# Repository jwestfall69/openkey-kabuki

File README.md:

# openkey-kabuki
* [Overview](#overview)
* [Project Status](#project-status)
* [Supported Games](#supported-games)
  * [Mitchell](#mitchell)
  * [CPS 1.5 (QSound CPU)](#cps-15-qsound-cpu)
* [Hardware](#hardware)
  * [PCB Manufacturing](#pcb-manufacturing)
  * [BOM](#bom)
  * [Assembly](#assembly)
* [Programming](#programming)
  * [Hardware](#hardware-1)
  * [Software](#software)
* [Installation](#installation)
  * [Mitchell DBS Identify/Removal](#mitchell-dbs-identifyremoval)
  * [CPS 1.5 (QSound CPU) DBS Identify/Removal](#cps-15-qsound-cpu-dbs-identifyremoval)

## Overview
This is an opensource/hardware implementation of an on the fly kabuki CPU key programmer that consists of a PCB that sits between the CPU socket and the kabuki CPU.  The kabuki CPU is found in Mitchell and CPS 1.5 arcade boards and contains keys for decrypting/decoding the program roms.

Installed:<br>

This project is providing the same functionality as [Undamned's InfiniKey-Kabuki](https://www.arcade-projects.com/threads/infinikey-kabuki.8338/).  The lack of supply is what prompted me to make openkey-kabuki.  If they ever end up coming back in stock please consider purchasing those to support [Undamned](https://www.arcade-projects.com/forums/temple-of-the-undamned.77/)'s work.

Details on *how* to program a kabuki CPU's key data can be found in [Eduardo Cruz](http://arcadehacker.blogspot.com/)'s [write up](http://arcadehacker.blogspot.com/2014/11/capcom-kabuki-cpu-intro.html) and [youtube video](https://www.youtube.com/watch?v=9t-9hQEOjLI).

Details on *what* to program can be found in MAME's decryption code for the [kabuki CPU](https://github.com/mamedev/mame/blob/master/src/mame/capcom/kabuki.cpp#L73).

## Project Status
**PCB:** I would consider the design PCB done at this point.  I'm open to any input on changes/improvements as this is my first PCB design.

**Firmware:** Need to get untested games tested

**Documentation:** Done

## Supported Games
openkey-kabuki supports either having a 5 position switch or using solder jumpers for picking which game key to use.  For the switch, ensure the switches are fully set.  You should hear a click sound as you change the position.

Below is a list of supported games and what switches/jumpers must be used for each.

#### Mitchell
| Switch<br>12345 | Program ROM Labels | MAME Sets | Game Names | Tested / Working |
|-----------------|:------------------:|-----------|--------------|:-----------------:|
| 00000 | BLE<br>BLJ | block<br>blockj | Block Block | YES (conversion)|
| 00001 | CBJ | cbasebal | Capcom Baseball | |
| 00010 | CW | cworld | Capcom World | YES (conversion) |
| 00011 | D2 | dokaben2 | Dokaben 2 | YES (conversion) |
| 00100 | DB | dokaben | Dokaben | YES (conversion) |
| 00101 | MG2 | mgakuen2 | Mahjong Gakuen 2 Gakuen-chou no Fukushuu | YES |
| 00110 | MG3 | marukin | Super Marukin-Ban | YES (conversion) |
| 00111 | PK<br>PKO | pkladiesl<br>pkladies | Poker Ladies | YES (conversion) |
| 01000 | PWE<br>PWJ<br>PWU | pang<br>pompingw<br>bbros | Pang<br>Pomping World<br>Buster Bros | YES |
| 01001 | Q2 | hatena | Adventure Quiz 2 - Hatena? no Daibouken | YES (conversion) |
| 01010 | Q3 | qtono1 | Quiz Tonosama no Yabou | YES |
| 01011 | Q4 | qsangoku | Quiz Sangokushi | YES |
| 01100 | SPE | spang | Super Pang (World) | YES |
| 01101 | SPJ | spangj | Super Pang (Japan) | YES |
| 01110 | SPU | sbbros | Super Buster Bros | YES |
| 01111 | ??? | ??? | Ashita Tenki ni Naare  (place holder) | |

#### CPS 1.5 (QSound CPU)
| Switch<br>12345 | Program ROM Labels | MAME Sets | Game Names | Tested / Working |
|-----------------|:------------------:|-----------|--------------|:-----------------:|
| 10000 | CDE<br>CDJ<br>CDT<br>CDU | dino<br>dinoj<br>dinoa<br>dinou | Cadillacs and Dinosaurs | |
| 10001 | MBE<br>MBJ<br>MBU<br>MBDE<br>MBDJ | slammast<br>mbomberj<br>slammastu<br>mbombrd<br>mbombrdj | Saturday Night Slam Masters<br>Muscle Bomber<br>Muscle Bomber Duo | YES |
| 10010 | PSE<br>PSH<br>PSJ<br>PSE | punisher<br>punisherh<br>punisherj<br>punisheru | Punisher | YES |
| 10011 | TK2A<br>TK2E<br>TK2J<br>TK2U | wofa<br>wof<br>wofj<br>wofu | Warriors of Fate | YES |

**IMPORTANT**: There is a compatibility issue with the older 92636D-3 revision of the D board.  Specifics on this issue can be found [here](https://www.arcade-projects.com/threads/openkey-kabuki-project.23571/post-370690)

When openkey-kabuki is used on a 92636D-3 board revision you will get:

  * "RAM ERROR" screen on Warriors of Fate
  * "1111 EXCEPTION" screen on Slam Masters
  * "NG" screen on Muscle Bomber Duo
  * A black screen on Punisher and C&D

Thus far I've only seen WOF using this older version of the D board.

The compatibility issue was tracked down to a bug in the D9K1 PAL thats on 92636D-3.  The fix is to upgrade that PAL to D9K2, which is found on the newer revision of the D board (92636D-5).

## Hardware
---
#### PCB Manufacturing
You will want to pick **0.8mm PCB thickness** instead of the default of 1.6mm.  A 1.6mm thick PCB will make the legs on openkey-kabuki to be a little to short and cause it to not be fully secure in the CPU socket.

I've been using [jlcpcb](https://jlcpcb.com/) for PCB manufacturing.  The only real downside I've seen with them is they charge a fee (~$17) if you pick a color other then green or black with 0.8mm PCB thickness.  Also watch out, by default they will add an order number to the silk screen unless you tell them not to.

#### BOM
| Description | Part Number | DigiKey | Mouser | Notes |
|-------------|-------------|---------|--------|-------|
| 40 Pin Dip Machine Socket | Adam Tech ICM-640-1-GT-HT | [2057-ICM-640-1-GT-HT-ND](https://www.digikey.com/en/products/detail/adam-tech/ICM-640-1-GT-HT/9832971) | | The specific part number isn't required, but it must be a machined 40 pin dip socket with the cross members in the same locations as seen in the picture at the top of this page. This [part](https://www.aliexpress.us/item/2251832711755702.html) from Aliexpress worked for me as well. |
| ATtiny404 20Mhz | ATTINY404-SSN | [ATTINY404-SSN-ND](https://www.digikey.com/en/products/detail/microchip-technology/ATTINY404-SSN/9947546) | [556-ATTINY404-SSNR](https://www.mouser.com/ProductDetail/Microchip-Technology-Atmel/ATTINY404-SSNR?qs=F5EMLAvA7IAEqD7Aw0z%252B9Q%3D%3D) | Other ATtiny tinyAVR 0/1/2-series models should be viable as well.  The code compiles to just over 1K in size, so any that have 2k or more of flash should work.  Just note I have only tested with 404s |
| 100nf / 0.1uf SMD Ceramic Capacitor 0805 Size | | | | |
| 5 Position Slide Switch | Würth Elektronik 416131160805 | [732-3855-2-ND](https://www.digikey.com/en/products/detail/w%C3%BCrth-elektronik/416131160805/3174531) | [710-416131160805](https://www.mouser.com/ProductDetail/Wurth-Elektronik/416131160805?qs=2kOmHSv6VfT1rqUsojuQog%3D%3D) | **Optional** not needed if using the solder jumpers to pick the game.  This part more then doubles the BOM cost. |

**NOTE**: Additional components maybe needed if you need to revert any previously made desuicide modifications to the arcade PCB.  Check the Installation section at the bottom for details.

#### Assembly
The first thing you should do is a test fit of the socket into the openkey-kabuki PCB.  I came across a couple PCBs in a batch that didn't fit and wasn't until after I had soldered the SMD components that I found this out.

As you can see in the first socket in the picture below the pins start out wide then go skinny.  Normally the wide part is used to keep the socket up off a board, however the openkey-kabuki PCB has extra wide through holes to allow it to sit flush with the plastic part of the socket.  Doing this allows the pins from the socket to be long enough to fit properly into the CPU socket of the arcade board.

You should solder the SMD components first.  Take special care to void getting any solder into any of the socket through holes.

  * If you install the dip switch block I would advise testing it
  * If you are using the solder jumpers instead, these can be done now or after everything is fully assembled.

When soldering the socket its best to not use a ton of solder.  The below picture is a board where the socket hasn't been soldered in yet.

Note the small gap between the through holes and socket pins.  Solder will naturally want to wick up into that gap.  I generally just use enough solder so that the gap around the socket pin becomes filled.

Once you have completed soldering the socket you should check the skinny part of the pins to verify there aren't any solder blobs on them.  These could cause damage to the CPU socket.

## Programming
#### Hardware
Programming is done with a UPDI programmer.  I've been using this one:

[Serial UPDI Programmer for ATmega 0-Series, or ATtiny 0-Series or 1-Series, or AVR DA or AVR DB](https://www.amazon.com/dp/B09X64YRLD?psc=1&ref=ppx_yo2ov_dt_b_product_details)

Note: This programmer (and likely others) has a switch for 3.3V and 5V.  Set it to 5V.

The openkey-kabuki programming port is setup so you can wedge the pins from the above programmer directly into them to programming.

Of course be sure you properly orient the board so the labeled pin/holes match up.  vcc to vcc, gnd to gnd, and updi to updi.

#### Software
For software I've been using the [Arduino IDE](https://www.arduino.cc/en/software/OldSoftwareReleases) with [megaTinyCore](https://github.com/SpenceKonde/megaTinyCore), which adds support for tinyAVR 0/1/2-Series MCUs.

**NOTE**: The makers of megaTinyCore currently recommend using Arduino IDE version 1.8.13 for best compatibility.  2.0 definitely does not work!

To install the megaTinyCore you, should just need to add http://drazzy.com/package_drazzy.com_index.json to "Additional Boards Manager URLs" in the settings for the Arduino IDE.

From there you need to configure the board/programming settings.  I've been using these:

## Installation
Prior to installing openkey-kabuki you should verify you don't have the [The Dead Battery Society](http://www.arcadecollecting.com/dead/) mod installed on your mitchell or cps 1.5 D board.  Part of the DBS mod is to tie pin 28 of the kabuki CPU to GND.  This pin is normally fed voltage from the battery/vcc to supply the CPU with power for its internal ram holding the key data.  openkey-kabuki will not function unless this is reverted.

Below is how you can identify if the DBS mod is been installed and how to remove it.

#### Mitchell DBS Identify/Removal
This is what a dead battery society mod will look like

 * R33 (1k ohm resistor) is missing
 * Right through hole of R33 is bridged to the lower right
 * Those pins on the program roms are soldered together and have a wire from them to a pin on the cpu
 * Modified program roms

 All of these things will need to be reverted in order to use openkey-kabuki.  This is what an unmodified board should look like.

#### CPS 1.5 (QSound CPU) DBS Identify/Removal

This is what the dead battery society mod will look like on the QSound board of a cps 1.5 game.

Top Side:<br>

* R33 (1 ohm resistor 0805 size) is missing
* C12 (100nf capacitor 0805 size) is replaced with a jumper
* Modified QSound program rom

Bottom Side:<br>

* Wire running from QSound program rom pin 30 to Kabuki CPU pin 27
* Cut trace between QSound program rom pins 30 and 31

There will be additional changes specific to slam masters / muscle bomber which are not covered above.

Once reverted it should look like this

Top Side:<br>

Bottom Side:<br>

Its hard to tell from the picture, but pins 30 and 31 on the QSound program rom are jumper'd together.

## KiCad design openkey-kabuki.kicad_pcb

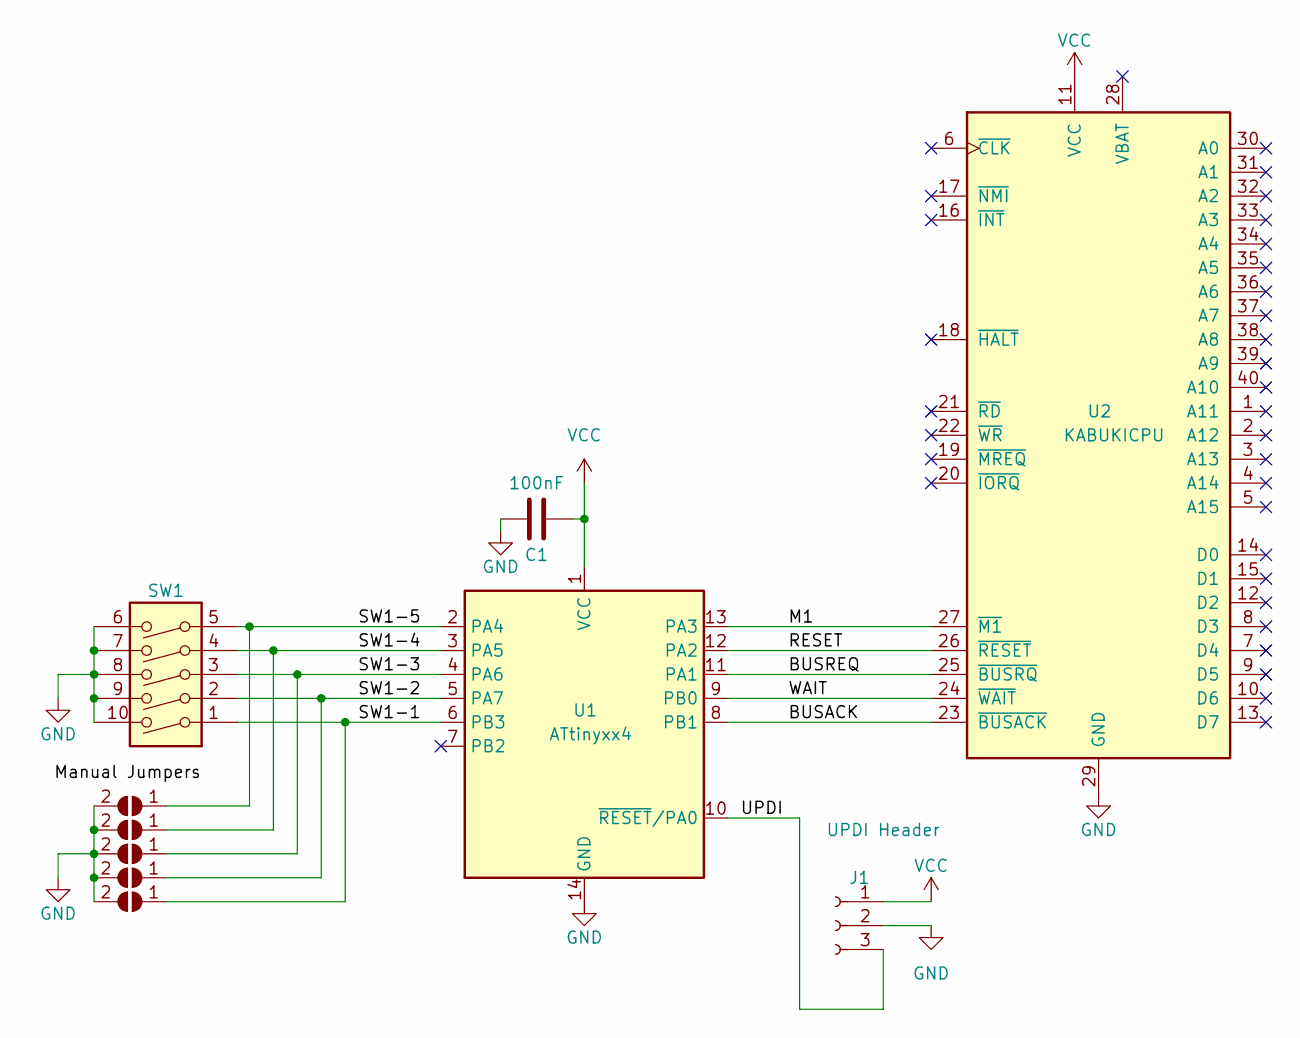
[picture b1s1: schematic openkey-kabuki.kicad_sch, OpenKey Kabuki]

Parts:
C1: 100nF; C_0805_2012Metric_Pad1.18x1.45mm_HandSolder
J1: UPDI Header; PinHeader_1x03_P2.54mm_Vertical
JP1, JP2, JP3, JP4, JP5: SolderJumper_2_Open; SolderJumper-2_P1.3mm_Open_Pad1.0x0.6mm
SW1: Wurth Elektronik 416131160805; SW_DIP_SPSTx05_Slide_Wurth_416131160805_W7.62mm_P1.27mm
U1: ATtinyxx4; SOIC-14_3.9x8.7mm_P1.27mm
U2: KABUKICPU; DIP-40_W15.24mm_Socket_Wide_Holes

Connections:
/BUSACK: U1.8 (PB1), U2.23 (~BUSACK)
/BUSREQ: U1.11 (PA1), U2.25 (~BUSRQ)
/M1: U1.13 (PA3), U2.27 (~M1)
/RESET: U1.12 (PA2), U2.26 (~RESET)
/SW1-1: JP1.1 (A), SW1.1, U1.6 (PB3)
/SW1-2: JP2.1 (A), SW1.2, U1.5 (PA7)
/SW1-3: JP3.1 (A), SW1.3, U1.4 (PA6)
/SW1-4: JP4.1 (A), SW1.4, U1.3 (PA5)
/SW1-5: JP5.1 (A), SW1.5, U1.2 (PA4)
/UPDI: J1.3, U1.10 (~RESET/PA0)
/WAIT: U1.9 (PB0), U2.24 (~WAIT)
GND: C1.2, J1.2, JP1.2 (B), JP2.2 (B), JP3.2 (B), JP4.2 (B), JP5.2 (B), SW1.6, SW1.7, SW1.8, SW1.9, SW1.10, U1.14 (GND), U2.29 (GND)
VCC: C1.1, J1.1, U1.1 (VCC), U2.11 (VCC)

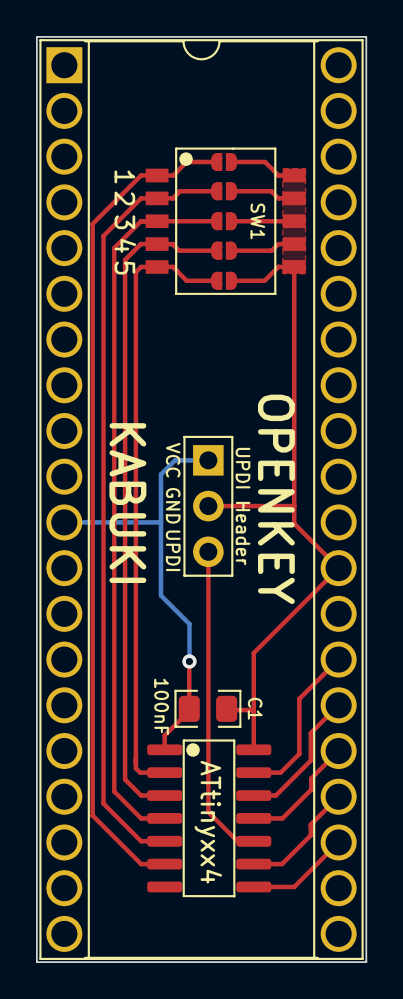
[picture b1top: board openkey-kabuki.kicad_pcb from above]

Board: 2 copper layers, 18.3 x 51.4 mm, 10 parts (0 on the bottom side), 13 nets.

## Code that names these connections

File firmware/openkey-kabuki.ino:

#include <avr/sleep.h>

// PIN 8 (PIN_B1) <=> Kabuki PIN 23 (BUSACK)
#define SET_BUSACK    PORTB.OUTSET = PIN1_bm
#define CLR_BUSACK    PORTB.OUTCLR = PIN1_bm

// PIN 9 (PIN_B0) <=> Kabuki PIN 24 (WAIT)
#define SET_WAIT      PORTB.OUTSET = PIN0_bm
#define CLR_WAIT      PORTB.OUTCLR = PIN0_bm

// PIN 10 (PIN_A0) used for UPDI (ATtiny programming)

// PIN 11 (PIN_A1) <=> Kabuki PIN 25 (BUSREQ)
#define SET_BUSREQ    PORTA.OUTSET = PIN1_bm
#define CLR_BUSREQ    PORTA.OUTCLR = PIN1_bm

// PIN 12 (PIN_A2) <=> Kabuki PIN 26 (RESET)
#define SET_RESET     PORTA.OUTSET = PIN2_bm
#define CLR_RESET     PORTA.OUTCLR = PIN2_bm

// PIN 13 (PIN_A3) <=> Kabuki PIN 27 (M1)
#define SET_M1        PORTA.OUTSET = PIN3_bm
#define CLR_M1        PORTA.OUTCLR = PIN3_bm

// First 4 fields come from mame @
// https://github.com/mamedev/mame/blob/master/src/mame/capcom/kabuki.cpp#L73
// mem_mask field comes from Eduardo Cruz (ArcadeHacker). 
// https://github.com/ArcadeHacker/ArcadeHacker_Kabuki/blob/master/ArcadeHacker_Kabuki.ino#L33
typedef struct game_key_t {
  uint32_t swap_key1;
  uint32_t swap_key2;
  uint16_t address_key;
   uint8_t xor_key;
  uint16_t mem_mask;
} game_key;

#define MAX_GAME_NUM   20
game_key game_keys[MAX_GAME_NUM + 1] = {
  // mitchell games                                      dsw
  //   skey1       skey2     addr    xor   mask         12345
  { 0x02461357, 0x64207531, 0x0002, 0x01, 0x7000 },  // 00000 [BLx] Block Block (BLE, BLJ)
  { 0x01234567, 0x76543210, 0x6548, 0x24, 0x7000 },  // 00001 [CBJ] Capcom Baseball
  { 0x04152637, 0x40516273, 0x5751, 0x43, 0x7000 },  // 00010 [CW]  Capcom World
  { 0x76543210, 0x01234567, 0xaa55, 0xa5, 0x7000 },  // 00011 [D2]  Dokaben 2
  { 0x76543210, 0x01234567, 0xaa55, 0xa5, 0x7000 },  // 00100 [DB]  Dokaben
  { 0x76543210, 0x01234567, 0xaa55, 0xa5, 0x7000 },  // 00101 [MG2] Mahjong Gakuen 2 Gakuen-chou no Fukushuu
  { 0x54321076, 0x54321076, 0x4854, 0x4f, 0x7000 },  // 00110 [MG3] Super Marukin-Ban
  { 0x76543210, 0x01234567, 0xaa55, 0xa5, 0x7000 },  // 00111 [PKx] Poker Ladies (PK, PKO)
  { 0x01234567, 0x76543210, 0x6548, 0x24, 0xf000 },  // 01000 [PWx] Pang / Buster Bros / Pomping World (PWE, PWJ, PWU)
  { 0x45670123, 0x45670123, 0x5751, 0x43, 0x7000 },  // 01001 [Q2]  Adventure Quiz 2 Hatena ? no Dai-Bouken
  { 0x12345670, 0x12345670, 0x1111, 0x11, 0x7000 },  // 01010 [Q3]  Quiz Tonosama no Yabou
  { 0x23456701, 0x23456701, 0x1828, 0x18, 0x7000 },  // 01011 [Q4]  Quiz Sangokushi
  { 0x45670123, 0x45670123, 0x5852, 0x43, 0x7000 },  // 01100 [SPE] Super Pang World
  { 0x45123670, 0x67012345, 0x55aa, 0x5a, 0x7000 },  // 01101 [SPJ] Super Pang Japan
  { 0x45670123, 0x45670123, 0x2130, 0x12, 0x7000 },  // 01110 [SPU] Super Buster Bros
  { 0x00000000, 0x00000000, 0x0000, 0x00, 0x0000 },  // 01111 [???] Ashita Tenki ni Naare (unknown)

  // cps1.5 games                                        dsw
  //   skey1       skey2     addr    xor   mask         12345
  { 0x76543210, 0x24601357, 0x4343, 0x43, 0xff00 },  // 10000 [CDx] Cadillacs and Dinosaurs (CDE, CDJ, CDT, CDU)
  { 0x54321076, 0x65432107, 0x3131, 0x19, 0xff00 },  // 10001 [MBx] Slam Masters (MBDE, MBDJ, MBE, MBJ, MBU)
  { 0x67452103, 0x75316024, 0x2222, 0x22, 0xff00 },  // 10010 [PSx] Punisher (PS, PSE, PSH, PSU)
  { 0x01234567, 0x54163072, 0x5151, 0x51, 0xff00 },  // 10011 [TKx] Warrior of Fate (TK2A, TK2E, TK2J, TK2U)

  // bad dsw value / zero key
  { 0x00000000, 0x00000000, 0x0000, 0x00, 0x0000 }
};

// doing bit shifting takes a variable amount
// of time depending on the how far the shift
// is.  Using the below lookup table to keep
// a consistent clock period when masking a
// bit to send. 
uint32_t masks[32] = {
  0x00000001, 0x00000002, 0x00000004, 0x00000008,
  0x00000010, 0x00000020, 0x00000040, 0x00000080,
  0x00000100, 0x00000200, 0x00000400, 0x00000800,
  0x00001000, 0x00002000, 0x00004000, 0x00008000,
  0x00010000, 0x00020000, 0x00040000, 0x00080000,
  0x00100000, 0x00200000, 0x00400000, 0x00800000,
  0x01000000, 0x02000000, 0x04000000, 0x08000000,
  0x10000000, 0x20000000, 0x40000000, 0x80000000,
};

void setup() {
  
  // wait a bit for other IC's on the board to get
  // in their inital states
  delay(100);

  // wait for the WAIT pin on the kabuki to go high
  // before we do anything
  while(!PORTB.IN & PIN0_bm) { }
  
  // set the pins to kabuki as outputs
  PORTA.DIR = PIN1_bm | PIN2_bm | PIN3_bm;
  PORTB.DIR = PIN0_bm | PIN1_bm;

  // stage #1: set initial output states
  // https://www.youtube.com/watch?v=9t-9hQEOjLI&t=754s
  CLR_RESET;
  CLR_WAIT;
  CLR_BUSREQ;
  SET_M1;
  SET_BUSACK;

  // enable pull-ups on dsw pins
  PORTA.PIN4CTRL |= PORT_PULLUPEN_bm;  // PIN 2 (PIN_PA4) <=> DSW5
  PORTA.PIN5CTRL |= PORT_PULLUPEN_bm;  // PIN 3 (PIN_PA5) <=> DSW4
  PORTA.PIN6CTRL |= PORT_PULLUPEN_bm;  // PIN 4 (PIN_PA6) <=> DSW3
  PORTA.PIN7CTRL |= PORT_PULLUPEN_bm;  // PIN 5 (PIN_PA7) <=> DSW2
  PORTB.PIN3CTRL |= PORT_PULLUPEN_bm;  // PIN 6 (PIN_PB3) <=> DSW1

  // stage #2: door knock #1
  // https://www.youtube.com/watch?v=9t-9hQEOjLI&t=871s
  for(int i = 0;i < 3;i++) {
    SET_BUSREQ;
    CLR_BUSREQ;
  }

  // stage #3: unlock key
  // https://www.youtube.com/watch?v=9t-9hQEOjLI&t=1274s
  send_data(0xb7a45, 20, -1);

  // stage #4: door knock #2
  // https://www.youtube.com/watch?v=9t-9hQEOjLI&t=1433s
  for(int i = 0;i < 10;i++) {
    CLR_M1;
    SET_M1;
  }

  uint8_t game_num = read_dsw();
  if(game_num > MAX_GAME_NUM) {
    game_num = MAX_GAME_NUM;
  }

  // stage #5: 108-bit programming
  // https://www.youtube.com/watch?v=9t-9hQEOjLI&t=1518s
  send_data(0x0, 20, -1);
  send_data(game_keys[game_num].address_key, 16, -1);

  // mame swap keys are 32bit, but the actual swap key is 24bit.
  // the conversion process is to drop the top bit from each nibble.
  // below we are looping over each nibble and only sending the
  // lower 3 bits.
  for(int start_bit = 30; start_bit > 0; start_bit -= 4) {
    send_data(game_keys[game_num].swap_key2, 3, start_bit);
  }

  for(int start_bit = 30; start_bit > 0; start_bit -= 4) {
    send_data(game_keys[game_num].swap_key1, 3, start_bit);
  }

  send_data(game_keys[game_num].xor_key, 8, -1);
  send_data(game_keys[game_num].mem_mask, 16, -1);

  // set all pins to be inputs
  PORTA.DIR = 0;
  PORTB.DIR = 0;

  // power down
  set_sleep_mode(SLEEP_MODE_PWR_DOWN);
  sleep_enable();
  sleep_cpu();
}

void loop() {
  while(1) {}
}

// send bits of data starting at start_bit and going MSB to LSB.
// if start_bit is -1, send the last LSB num_bits bits of the data
void send_data(uint32_t data, int8_t num_bits, int8_t start_bit) {
  num_bits--;

  if(start_bit == -1) {
    start_bit = num_bits;
  }

  while(num_bits >= 0) {
    uint32_t bit = data & masks[start_bit];
    if(bit) {
      SET_M1;
    } else {
      CLR_M1;
    }
    CLR_BUSACK;
    SET_BUSACK;
    num_bits--;
    start_bit--;
  }
}

// DSW1 = PB3 = bit4
// DSW2 = PA7 = bit3
// DSW3 = PA6 = bit2
// DSW4 = PA5 = bit1
// DSW5 = PA4 = bit0
uint8_t read_dsw() {
  uint8_t dsw = 0;

  // negate the bits since we are using
  // pull-ups, "on"s will be low
  uint8_t porta = PORTA.IN ^ 0xff;
  uint8_t portb = PORTB.IN ^ 0xff;

  dsw = porta >> 4;
  dsw = dsw | ((portb & 0b0001000) << 1);
  return dsw;
}

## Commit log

2022-10-11 initial checkin
2022-10-11 Add openkey-kicad-library as submodule
2022-10-11 board checkin
2022-10-11 Move hardware bits under hardware dir
2022-10-11 Checkin firmware
2022-10-12 Move firmware to a openkey-kabuki sub dir to keep arduino ide happy
2022-10-12 Add exported gerber directories to .gitignore
2022-10-22 Add some docs
2022-10-23 More Docs
2022-10-25 Add cap/resistor physical sizes for cps 1.5 dbs revert
2022-10-25 Doc cleanup / fixes
2022-10-26 Add TOC to Docs
2022-10-29 mgakuen2 is tested
2022-10-29 Doc fixes
2022-10-29 Adjust TOC to work with github
2022-10-30 Docs: Suggest doing a test fit of socket before any soldering
2022-11-16 Docs: Add project status and other minor changes
2022-11-17 Docs: programmer voltage switch
2022-11-26 slam masters tested thanks to JammaJames2k
2022-12-17 Quiz Sangokushi and Quiz Tonosama no Yabou are tested
    Got my hands on these boards and both tested good
2022-12-20 Capcom World and Adventure Quiz 2 tested
    I was able to make conversions of the games to test using my Quiz
    Sangokushi board.
2022-12-20 Poker Ladies and Super Marukin-Ban tested
    I was able to make conversions of the games to test using my Mahjong
    Gakuen 2 board.
2023-01-02 Rework some of the docs around installation and DBS removal
2023-01-02 Tweak last doc update
    Forgot in a previous hw rev I removed using pin 28 on the kabuki, so
    the short to ground wont happen if dbs mod is installed.
2023-03-19 Note about compatibility issue and fix with 92636D-3 D boards
    Couple spelling fixes too
